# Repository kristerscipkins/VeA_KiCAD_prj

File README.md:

# VeA_KiCAD_prj

repozitorijs paredzēts iespiedplašu versiju kontrolei

Ja  kādi jautājumi sūtiet jautājumus uz s20cipkkris@venta.lv

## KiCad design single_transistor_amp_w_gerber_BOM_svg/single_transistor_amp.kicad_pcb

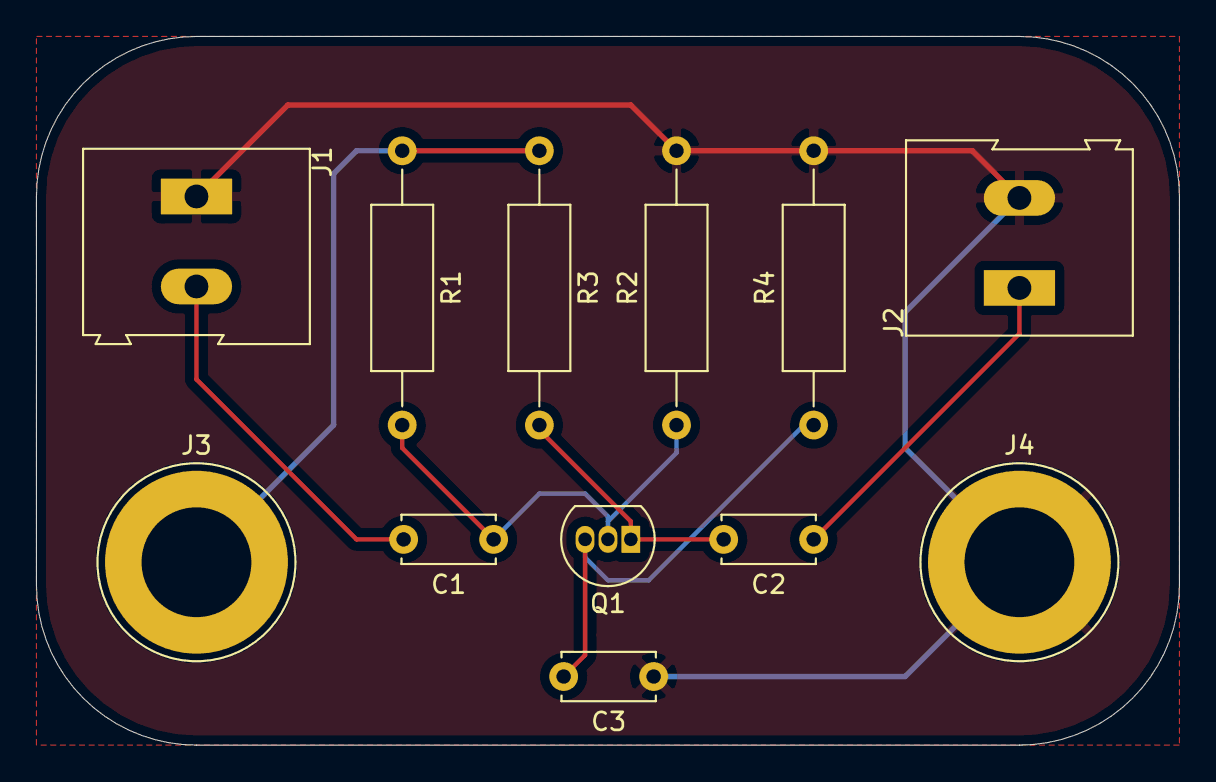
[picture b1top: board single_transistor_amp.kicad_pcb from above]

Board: 2 copper layers, 63.5 x 39.4 mm, 12 parts (0 on the bottom side), 7 nets.

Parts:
C1, C2: 20uF; C_Disc_D5.0mm_W2.5mm_P5.00mm
C3: 50uF; C_Disc_D5.0mm_W2.5mm_P5.00mm
J1, J2: Screw_Terminal_01x02; TerminalBlock_Altech_AK300-2_P5.00mm
J3, J4: Screw_Terminal_01x01; Banana_Jack_1Pin
Q1: BC548; TO-92_Inline
R1: 22k; R_Axial_DIN0309_L9.0mm_D3.2mm_P15.24mm_Horizontal
R2: 6.8k; R_Axial_DIN0309_L9.0mm_D3.2mm_P15.24mm_Horizontal
R3: 4.7k; R_Axial_DIN0309_L9.0mm_D3.2mm_P15.24mm_Horizontal
R4: 1.8k; R_Axial_DIN0309_L9.0mm_D3.2mm_P15.24mm_Horizontal

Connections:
+12V: J3.1, R1.1, R3.1
GNDREF: C3.1, J1.1, J2.2, J4.1, R2.2, R4.2
unnamed: C1.1, Q1.2, R1.2, R2.1
unnamed: C1.2, J1.2
unnamed: C2.1, J2.1
unnamed: C2.2, Q1.1, R3.2
unnamed: C3.2, Q1.3, R4.1
